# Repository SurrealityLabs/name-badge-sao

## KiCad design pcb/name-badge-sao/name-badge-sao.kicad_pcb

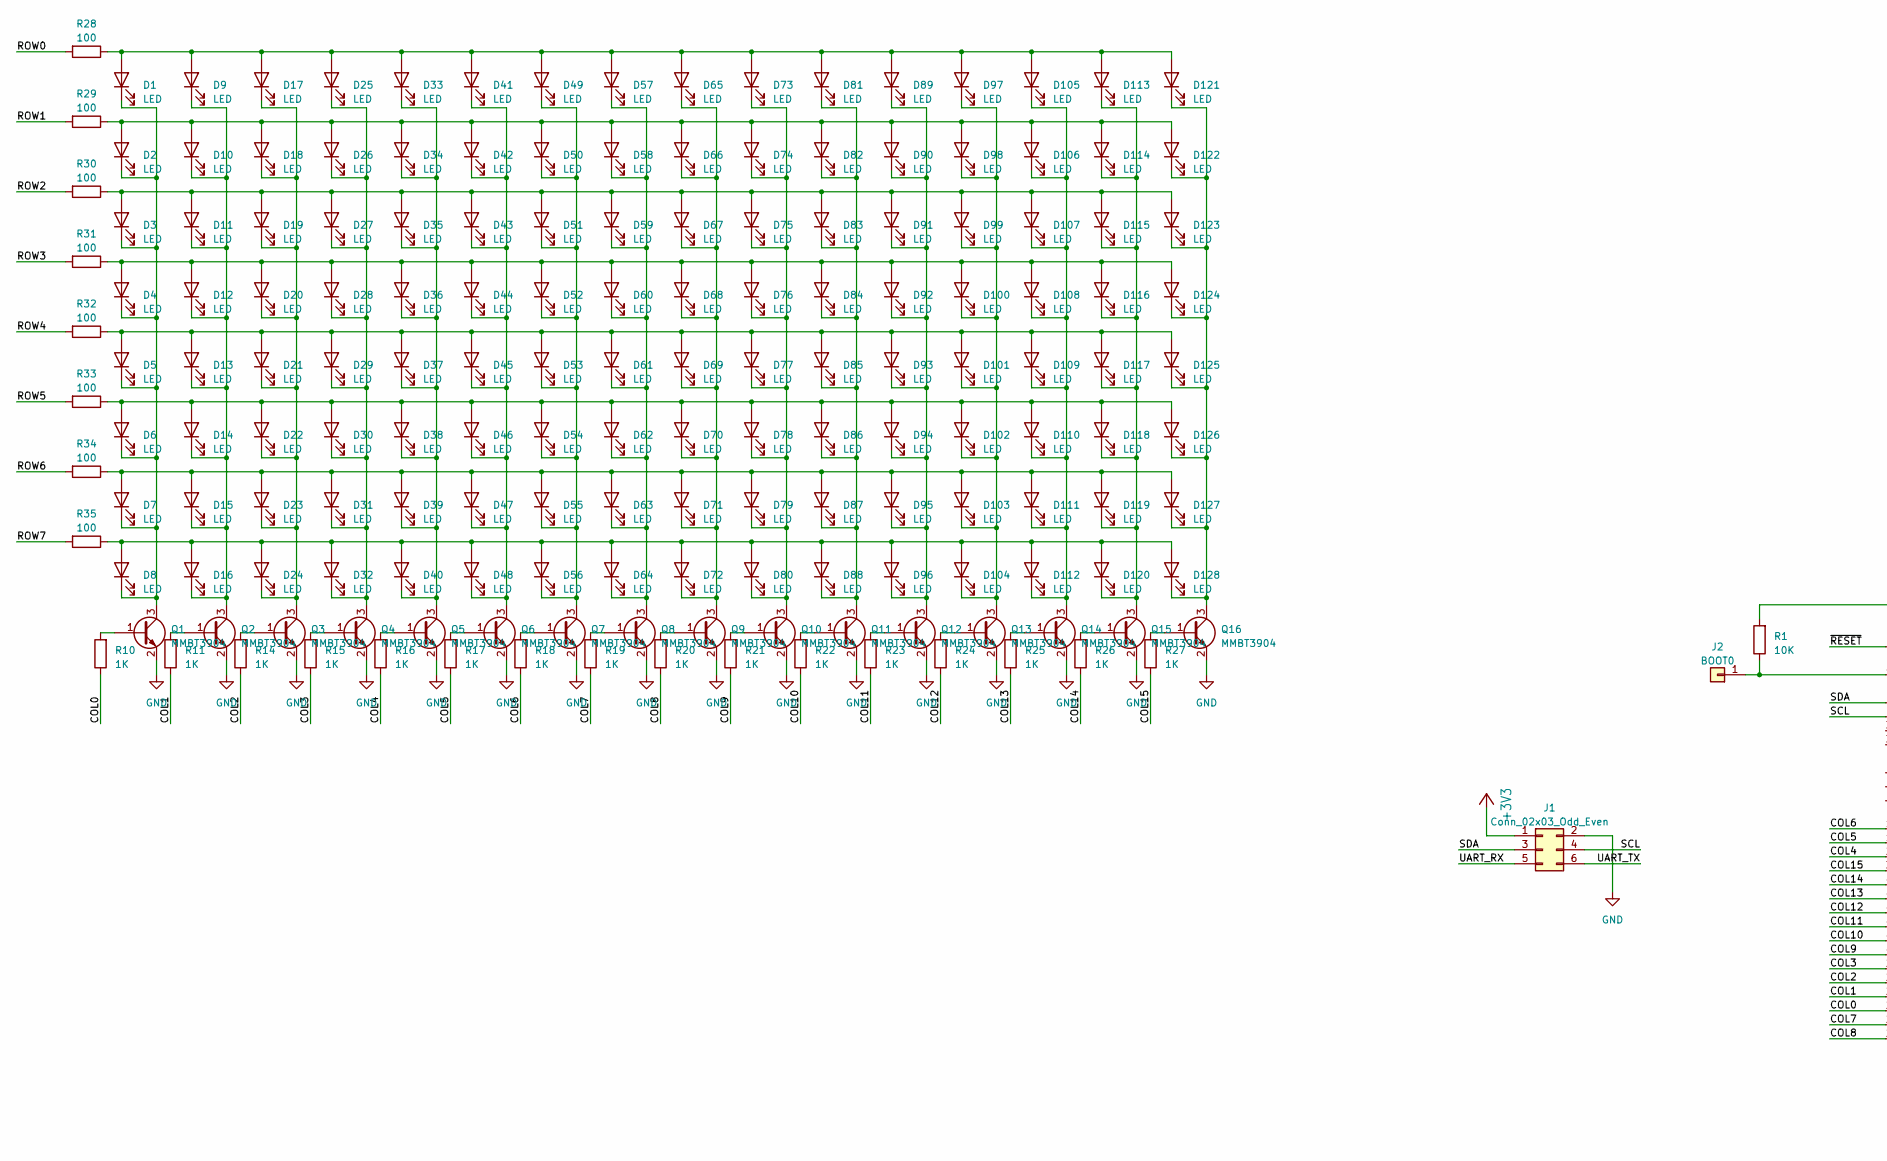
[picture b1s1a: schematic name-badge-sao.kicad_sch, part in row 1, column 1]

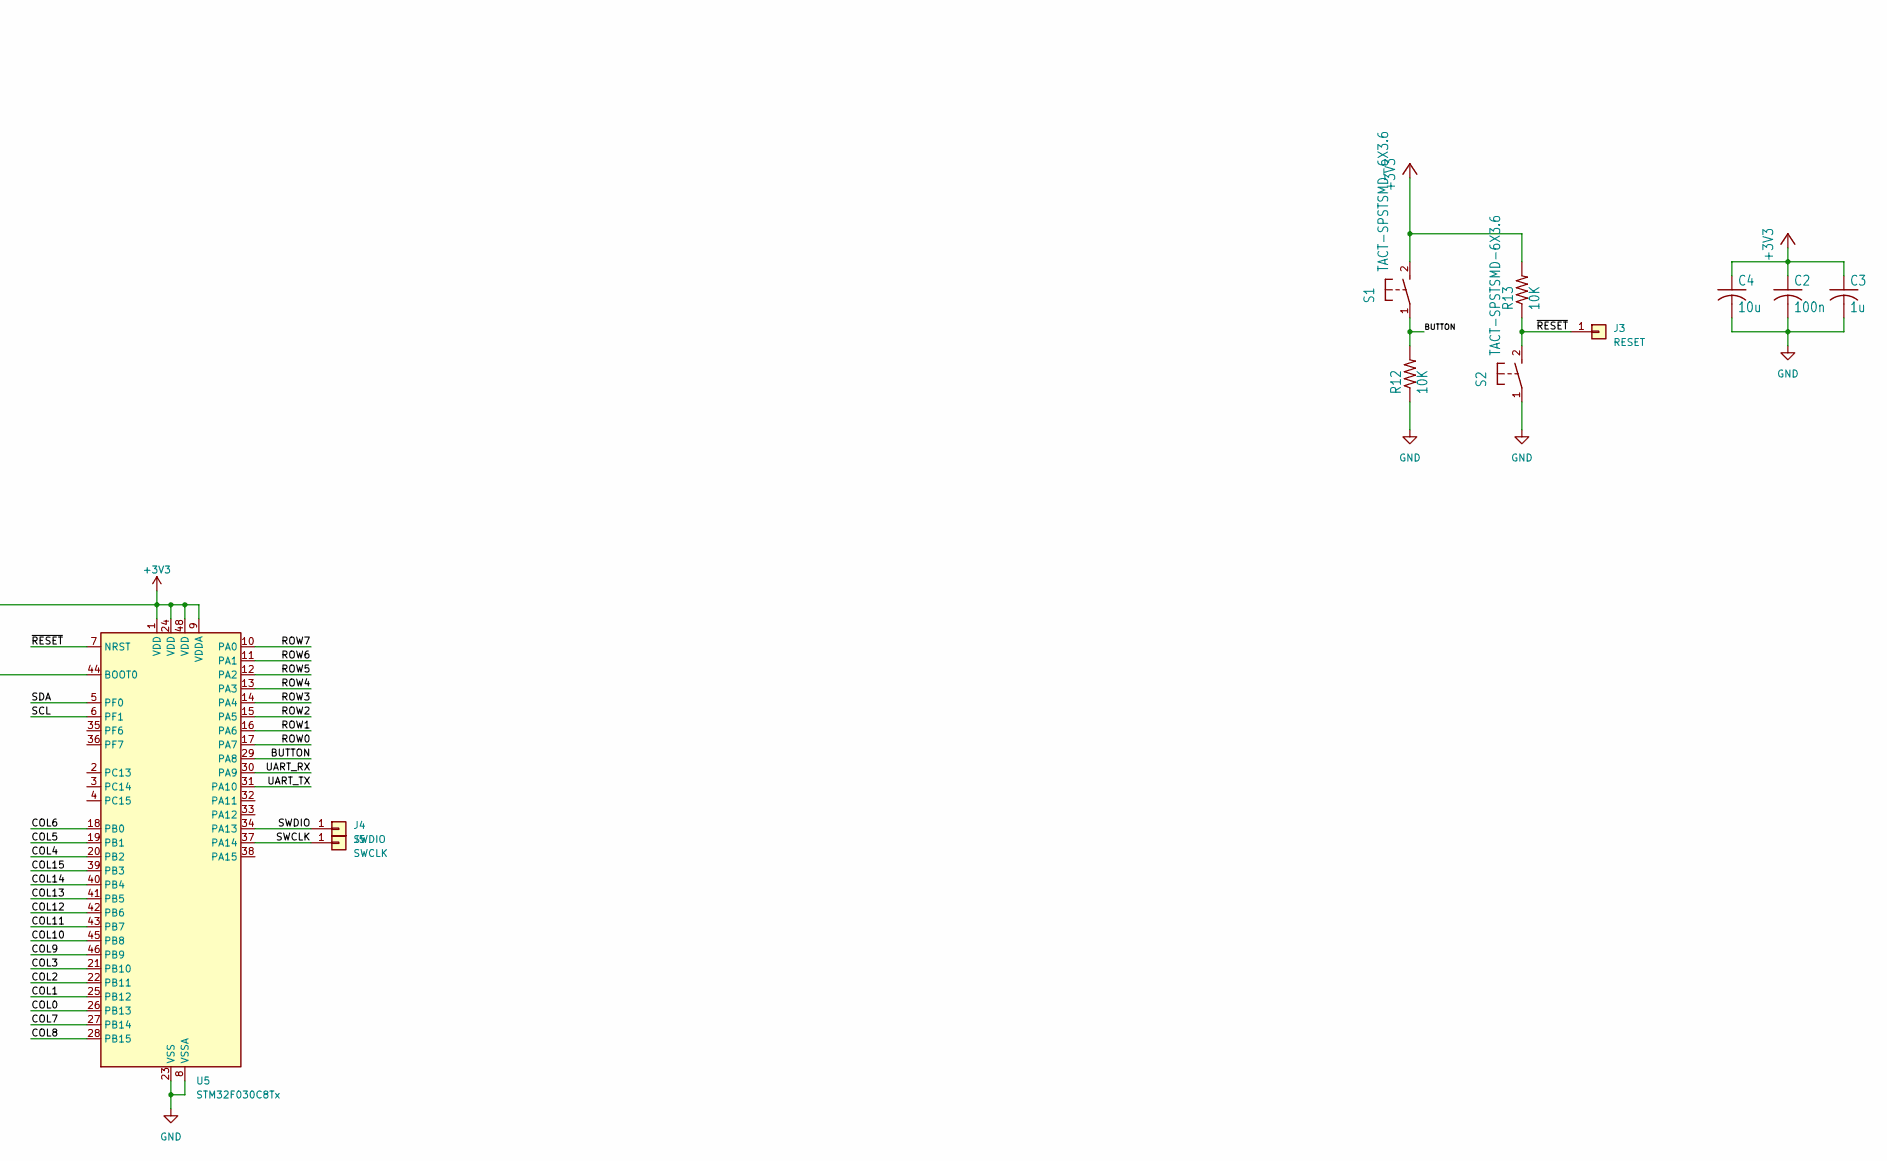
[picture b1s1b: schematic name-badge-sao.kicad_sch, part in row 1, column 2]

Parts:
C2: 100n; C_0603_1608Metric; LCSC C14663
C3: 1u; C_0603_1608Metric; LCSC C15849
C4: 10u; C_0805_2012Metric; LCSC C15850
D1, D2, D3, D4, D5, D6, D7, D8, D9, D10, D11, D12, D13, D14, D15, D16, D17, D18, D19, D20, D21, D22, D23, D24, D25, D26, D27, D28, D29, D30, D31, D32, D33, D34, D35, D36, D37, D38, D39, D40, D41, D42, D43, D44, D45, D46, D47, D48, D49, D50, D51, D52, D53, D54, D55, D56, D57, D58, D59, D60, D61, D62, D63, D64, D65, D66, D67, D68, D69, D70, D71, D72, D73, D74, D75, D76, D77, D78, D79, D80, D81, D82, D83, D84, D85, D86, D87, D88, D89, D90, D91, D92, D93, D94, D95, D96, D97, D98, D99, D100, D101, D102, D103, D104, D105, D106, D107, D108, D109, D110, D111, D112, D113, D114, D115, D116, D117, D118, D119, D120, D121, D122, D123, D124, D125, D126, D127, D128: LED; LED_0603_1608Metric
J1: Conn_02x03_Odd_Even; IDC-Header_2x03_P2.54mm_Vertical_SMD
J2: BOOT0; TestPoint_Pad_1.5x1.5mm
J3: RESET; TestPoint_Pad_1.5x1.5mm
J4: SWDIO; TestPoint_Pad_1.5x1.5mm
J5: SWCLK; TestPoint_Pad_1.5x1.5mm
Q1, Q2, Q3, Q4, Q5, Q6, Q7, Q8, Q9, Q10, Q11, Q12, Q13, Q14, Q15, Q16: MMBT3904; SOT-23
R1: 10K; R_0603_1608Metric
R10, R11, R14, R15, R16, R17, R18, R19, R20, R21, R22, R23, R24, R25, R26, R27: 1K; R_0603_1608Metric
R12, R13: 10K; R_0603_1608Metric; LCSC C25804
R28, R29, R30, R31, R32, R33, R34, R35: 100; R_0603_1608Metric
S1, S2: TACT-SPSTSMD-6X3.6; SW_SPST_FSMSM; LCSC C410373
U5: STM32F030C8Tx; LQFP-48_7x7mm_P0.5mm

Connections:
+3V3: C2.1, C3.1, C4.1, J1.1, R1.2, R13.2, S1.2 (S), U5.1 (VDD), U5.9 (VDDA), U5.24 (VDD), U5.48 (VDD)
/BUTTON: R12.2, S1.1, U5.29 (PA8)
/COL0: R10.1, U5.26 (PB13)
/COL1: R11.1, U5.25 (PB12)
/COL2: R14.1, U5.22 (PB11)
/COL3: R15.1, U5.21 (PB10)
/COL4: R16.1, U5.20 (PB2)
/COL5: R17.1, U5.19 (PB1)
/COL6: R18.1, U5.18 (PB0)
/COL7: R19.1, U5.27 (PB14)
/COL8: R20.1, U5.28 (PB15)
/COL9: R21.1, U5.46 (PB9)
/COL10: R22.1, U5.45 (PB8)
/COL11: R23.1, U5.43 (PB7)
/COL12: R24.1, U5.42 (PB6)
/COL13: R25.1, U5.41 (PB5)
/COL14: R26.1, U5.40 (PB4)
/COL15: R27.1, U5.39 (PB3)
/ROW0: R28.2, U5.17 (PA7)
/ROW1: R29.2, U5.16 (PA6)
/ROW2: R30.2, U5.15 (PA5)
/ROW3: R31.2, U5.14 (PA4)
/ROW4: R32.2, U5.13 (PA3)
/ROW5: R33.2, U5.12 (PA2)
/ROW6: R34.2, U5.11 (PA1)
/ROW7: R35.2, U5.10 (PA0)
/SCL: J1.4, U5.6 (PF1)
/SDA: J1.3, U5.5 (PF0)
/SWCLK: J5.1, U5.37 (PA14)
/SWDIO: J4.1, U5.34 (PA13)
/UART_RX: J1.5, U5.30 (PA9)
/UART_TX: J1.6, U5.31 (PA10)
/~RESET: J3.1, R13.1, S2.2 (S), U5.7 (NRST)
GND: C2.2, C3.2, C4.2, J1.2, Q1.2 (E), Q2.2 (E), Q3.2 (E), Q4.2 (E), Q5.2 (E), Q6.2 (E), Q7.2 (E), Q8.2 (E), Q9.2 (E), Q10.2 (E), Q11.2 (E), Q12.2 (E), Q13.2 (E), Q14.2 (E), Q15.2 (E), Q16.2 (E), R12.1, S2.1, U5.8 (VSSA), U5.23 (VSS), U5.47 (VSS)
unnamed: D1.2 (A), D9.2 (A), D17.2 (A), D25.2 (A), D33.2 (A), D41.2 (A), D49.2 (A), D57.2 (A), D65.2 (A), D73.2 (A), D81.2 (A), D89.2 (A), D97.2 (A), D105.2 (A), D113.2 (A), D121.2 (A), R28.1
unnamed: D1.1 (K), D2.1 (K), D3.1 (K), D4.1 (K), D5.1 (K), D6.1 (K), D7.1 (K), D8.1 (K), Q1.3 (C)
unnamed: D2.2 (A), D10.2 (A), D18.2 (A), D26.2 (A), D34.2 (A), D42.2 (A), D50.2 (A), D58.2 (A), D66.2 (A), D74.2 (A), D82.2 (A), D90.2 (A), D98.2 (A), D106.2 (A), D114.2 (A), D122.2 (A), R29.1
unnamed: D9.1 (K), D10.1 (K), D11.1 (K), D12.1 (K), D13.1 (K), D14.1 (K), D15.1 (K), D16.1 (K), Q2.3 (C)
unnamed: D17.1 (K), D18.1 (K), D19.1 (K), D20.1 (K), D21.1 (K), D22.1 (K), D23.1 (K), D24.1 (K), Q3.3 (C)
unnamed: D25.1 (K), D26.1 (K), D27.1 (K), D28.1 (K), D29.1 (K), D30.1 (K), D31.1 (K), D32.1 (K), Q4.3 (C)
unnamed: D33.1 (K), D34.1 (K), D35.1 (K), D36.1 (K), D37.1 (K), D38.1 (K), D39.1 (K), D40.1 (K), Q5.3 (C)
unnamed: D41.1 (K), D42.1 (K), D43.1 (K), D44.1 (K), D45.1 (K), D46.1 (K), D47.1 (K), D48.1 (K), Q6.3 (C)
unnamed: D49.1 (K), D50.1 (K), D51.1 (K), D52.1 (K), D53.1 (K), D54.1 (K), D55.1 (K), D56.1 (K), Q7.3 (C)
unnamed: D57.1 (K), D58.1 (K), D59.1 (K), D60.1 (K), D61.1 (K), D62.1 (K), D63.1 (K), D64.1 (K), Q8.3 (C)
unnamed: D65.1 (K), D66.1 (K), D67.1 (K), D68.1 (K), D69.1 (K), D70.1 (K), D71.1 (K), D72.1 (K), Q9.3 (C)
unnamed: D73.1 (K), D74.1 (K), D75.1 (K), D76.1 (K), D77.1 (K), D78.1 (K), D79.1 (K), D80.1 (K), Q10.3 (C)
unnamed: D81.1 (K), D82.1 (K), D83.1 (K), D84.1 (K), D85.1 (K), D86.1 (K), D87.1 (K), D88.1 (K), Q11.3 (C)
unnamed: D89.1 (K), D90.1 (K), D91.1 (K), D92.1 (K), D93.1 (K), D94.1 (K), D95.1 (K), D96.1 (K), Q12.3 (C)
unnamed: D4.2 (A), D12.2 (A), D20.2 (A), D28.2 (A), D36.2 (A), D44.2 (A), D52.2 (A), D60.2 (A), D68.2 (A), D76.2 (A), D84.2 (A), D92.2 (A), D100.2 (A), D108.2 (A), D116.2 (A), D124.2 (A), R31.1
unnamed: D97.1 (K), D98.1 (K), D99.1 (K), D100.1 (K), D101.1 (K), D102.1 (K), D103.1 (K), D104.1 (K), Q13.3 (C)
unnamed: D5.2 (A), D13.2 (A), D21.2 (A), D29.2 (A), D37.2 (A), D45.2 (A), D53.2 (A), D61.2 (A), D69.2 (A), D77.2 (A), D85.2 (A), D93.2 (A), D101.2 (A), D109.2 (A), D117.2 (A), D125.2 (A), R32.1
unnamed: D6.2 (A), D14.2 (A), D22.2 (A), D30.2 (A), D38.2 (A), D46.2 (A), D54.2 (A), D62.2 (A), D70.2 (A), D78.2 (A), D86.2 (A), D94.2 (A), D102.2 (A), D110.2 (A), D118.2 (A), D126.2 (A), R33.1
unnamed: D7.2 (A), D15.2 (A), D23.2 (A), D31.2 (A), D39.2 (A), D47.2 (A), D55.2 (A), D63.2 (A), D71.2 (A), D79.2 (A), D87.2 (A), D95.2 (A), D103.2 (A), D111.2 (A), D119.2 (A), D127.2 (A), R34.1
unnamed: D8.2 (A), D16.2 (A), D24.2 (A), D32.2 (A), D40.2 (A), D48.2 (A), D56.2 (A), D64.2 (A), D72.2 (A), D80.2 (A), D88.2 (A), D96.2 (A), D104.2 (A), D112.2 (A), D120.2 (A), D128.2 (A), R35.1
unnamed: D105.1 (K), D106.1 (K), D107.1 (K), D108.1 (K), D109.1 (K), D110.1 (K), D111.1 (K), D112.1 (K), Q14.3 (C)
unnamed: D3.2 (A), D11.2 (A), D19.2 (A), D27.2 (A), D35.2 (A), D43.2 (A), D51.2 (A), D59.2 (A), D67.2 (A), D75.2 (A), D83.2 (A), D91.2 (A), D99.2 (A), D107.2 (A), D115.2 (A), D123.2 (A), R30.1
unnamed: D113.1 (K), D114.1 (K), D115.1 (K), D116.1 (K), D117.1 (K), D118.1 (K), D119.1 (K), D120.1 (K), Q15.3 (C)
unnamed: D121.1 (K), D122.1 (K), D123.1 (K), D124.1 (K), D125.1 (K), D126.1 (K), D127.1 (K), D128.1 (K), Q16.3 (C)
unnamed: J2.1, R1.1, U5.44 (BOOT0)
unnamed: Q1.1 (B), R10.2
unnamed: Q2.1 (B), R11.2
unnamed: Q3.1 (B), R14.2
unnamed: Q4.1 (B), R15.2
unnamed: Q5.1 (B), R16.2
unnamed: Q6.1 (B), R17.2
unnamed: Q7.1 (B), R18.2
unnamed: Q8.1 (B), R19.2
unnamed: Q9.1 (B), R20.2
unnamed: Q10.1 (B), R21.2
unnamed: Q11.1 (B), R22.2
unnamed: Q12.1 (B), R23.2
unnamed: Q13.1 (B), R24.2
unnamed: Q14.1 (B), R25.2
unnamed: Q15.1 (B), R26.2
unnamed: Q16.1 (B), R27.2

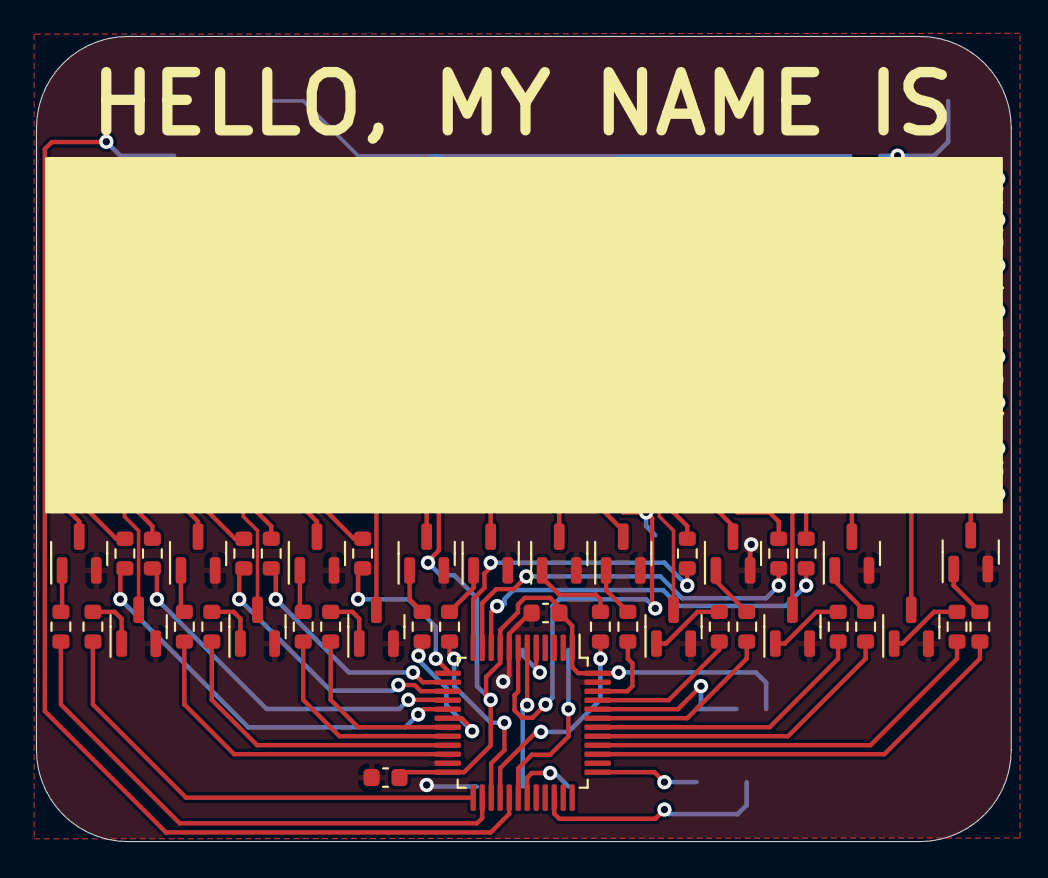
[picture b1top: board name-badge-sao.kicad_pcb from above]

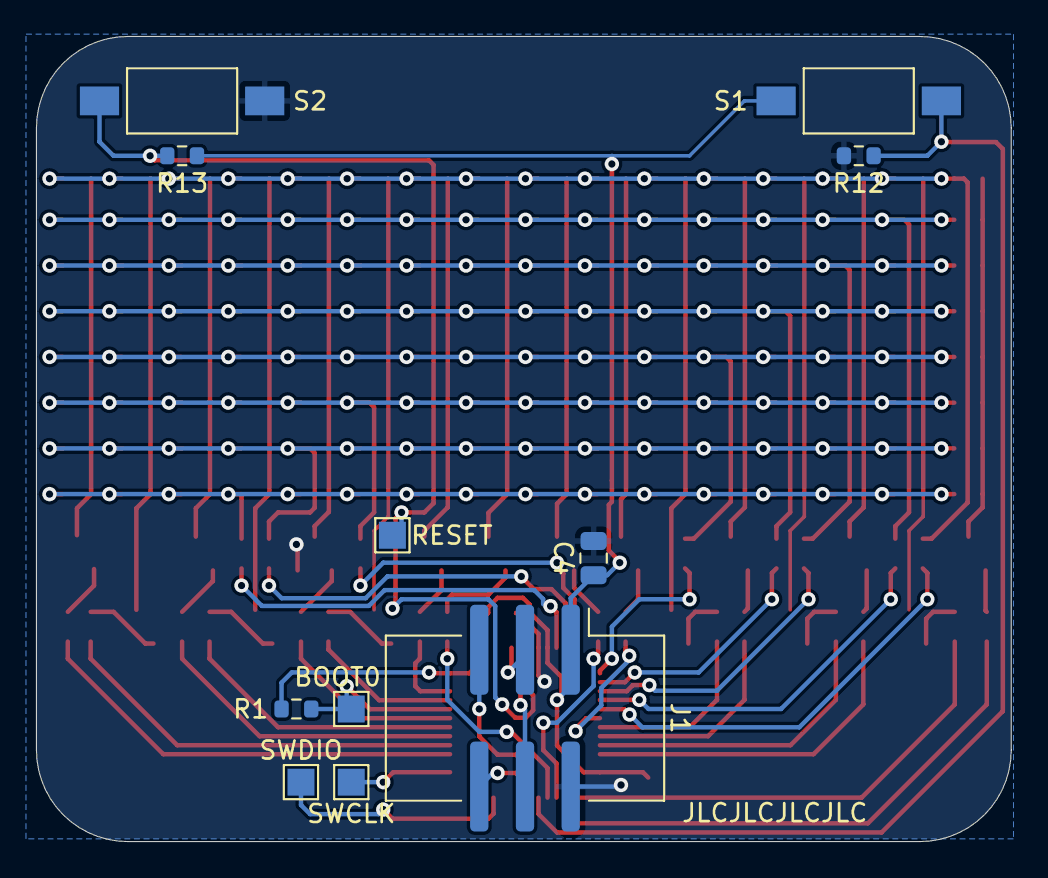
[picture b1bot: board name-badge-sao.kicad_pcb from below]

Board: 2 copper layers, 54.2 x 44.7 mm, 182 parts (11 on the bottom side), 75 nets.

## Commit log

2023-11-12 Adding first shot at SAO. Still need to decide if it'll be a full standalone badge, or just a display SAO.
2023-11-16 Moving to an all-new circuit design (normal matrix, no charlieplexing) with a new MCU, because why not change everything?
2023-11-17 I think that's an SAO
